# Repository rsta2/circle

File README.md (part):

Circle
======

Overview
--------

Circle is a C++ bare metal programming environment for the Raspberry Pi. It should be usable on most existing models (see "Support Status" below). Circle provides several ready-tested [C++ classes](doc/classes.txt) and [add-on libraries](addon/README), which can be used to control different hardware features of the Raspberry Pi. Together with Circle there are delivered several [sample programs](sample/README), which demonstrate the use of its classes. Circle can be used to create 32-bit or 64-bit bare metal applications.

Circle includes bigger (optional) third-party C-libraries for specific purposes in addon/ now. This is the reason why GitHub rates the project as a C-language-project. The main Circle libraries are written in C++ using classes instead. That's why it is called a C++ programming environment.

Disclaimer
----------

Circle is a free open-source project created by makers for makers. Because it targets bare-metal systems and is developed without formal QA or access to every hardware variant, it may not work as expected in all environments.

- **No warranty:** Circle is provided "as is" without any express or implied warranties, including merchantability, fitness for a particular purpose, or noninfringement.
- **Limited testing:** Contributors and maintainers test to the best of their ability but do not operate a dedicated testing department and cannot validate Circle on every device, bootloader version, or model revision.
- **User responsibility:** If you integrate Circle into a project - especially a commercial product (not recommended) - you are responsible for thoroughly testing the software in your target environment and for any consequences of its use.
- **Source-only distribution:** We publish Circle only as source code; no official binary releases are provided.
- **Risk acknowledgement:** By using Circle you acknowledge the residual risks associated with bare-metal development and accept responsibility for verifying suitability and safety for your use case.

Release 51.1.1
--------------

This hotfix release reverts a commit, which does not allow to use lld as the linker with Clang, which is planned to be used with circle-stdlib. Furthermore it comes with an additional sanity check for the 8BitDo gamepad drivers.

Release 51.1
------------

This release comes with **support for the Official 5" and 7" Touchscreens (v1 and v2)** with DSI interface **on the Raspberry Pi 5** in [addon/rp1dsi/](addon/rp1dsi). This can be tested with *sample/28-touchscreen* and *addon/lvgl/sample*. You have to set the `DSI_DISPLAY` variable in the respective *Makefile* to use the DSI displays.

Another attempt to **overcome the dropped USB MIDI events problem** on the Raspberry Pi 1-3 and Zero has been made. The *cmdline.txt* option `usbboost=` has been extended and gets a bit-masked decimal parameter now, where each bit 0-3 enables an option, which can help to fix such problems. See the [doc/cmdline.txt](doc/cmdline.txt) for a detailed description. `usbboost=15` enables all options, but does work only, when the USB MIDI controller is directly connected to the USB root port (without hub).

If you are using USB in FIQ mode on the Raspberry Pi 1-3 and Zero with the system option `USE_USB_FIQ`, you can try to enable the option `USB_MIDI_FIQ_COMPLETION` too to reduce the latency on delivering received MIDI events to the minimum. Your MIDI event packet handler must be able to run on `FIQ_LEVEL` in this case. Normally it runs on `IRQ_LEVEL`. Additionally you can define `USB_MIDI_CHECK_INCOMING` to validate incoming MIDI event packets, before calling the MIDI event packet handler.

More news:

* A new log severity `LogTrace` for frequent trace messages is introduced. Messages with this severity can be generated with the macro `LOGTRACE()`. Log messages of this kind are only displayed, when the option `loglevel=5` is specified in the file *cmdline.txt* on the SD card.
* A number of 8BitDo Xbox360 gamepads and keyboards is supported now.
* Support for USB mice with generic HID interface (3-0-0) has been added.
* FatFs has been updated to R0.16 with patch 2.

Fixes:

* An invalid handling of TCP ACK for fragmented modem sessions has been corrected. This also solved the issue of sending scrambled TCP data over low-speed/-quality network links.
* A race condition in `CSynchronizationEvent::Wait()` has been fixed, which could cause lost wake events, when this method had been called from an IRQ handler.
* A spurious hang caused by unexpected USB Disconnect events on cold boot has been fixed.
* Hidden WLAN SSIDs are supported now. You have to add the `scan_ssid=1` option for the hidden SSID to the file *wpa_supplicant.conf*.
* USB mass-storage gadget has speed auto-negotiation and a robust host reset/suspend handling now.
* Fixed that WLAN was unable to connect to eero7 router.

The 51st Step
-------------

This release offers a significantly improved implementation of the TCP/IP network stack. It supports TCP congestion control according to RFC 5681 with Fast Retransmit and Fast Recovery. Also the unnecessary copying of frames and data in the stack is largely prevented. This improves throughput very much, especially when a Raspberry Pi with 100 MBps Ethernet is connected to a Gigabit network.

The socket API is nearly unchanged, but the new `MSG_MORE` flag can be specified, when calling `CSocket::Send()` on TCP sockets, which prevents the immediate delivery of received data on the receiver side, when more data follows. `CSocket::Bind()` can be called with port 0 to bind to an ephemeral port, which can be requested using `CSocket::GetOwnPort()`. `CSocket::SendTo()` without preceding `Bind()` or `Connect()` is allowed too, which automatically assigns an ephemeral port.

Circle supports the extended C++ standard library support (LLVM libc++ port) in the [circle-stdlib](https://github.com/smuehlst/circle-stdlib) project in several ways (e.g. with the new `STDLIB_SUPPORT=4` level).

The recommended toolchain to build Circle applications is now based on GCC 15.2.Rel1. See the link in the Build section! Circle is built with `-std=c++17` by default now. There are options for selecting C++14 (previous default) and C++20 for the `configure` tool, beside the new `--kernel-max-size`, `--clang` and `--kasan` options. Enter `./configure --help` for more info!

The recommended firmware has been updated in *boot/*.

More new features:

* A `CDevice` instance can have property strings for vendor, product, serial number and function (e.g. the USB interface) now. These strings are assigned for all USB- and for NVMe devices, and can be used to distinguish devices of the same class. `CDeviceNameService::ListDevices()` can show these properties.
* The system option `USE_GPIO_MANAGER_FIQ` has been added. When an application needs multiple FIQ-triggered GPIO interrupt pins, the class `CGPIOPinFIQ` cannot be used. It is also not possible to use `CGPIOPinFIQ` together with the class `CGPIOManager` to handle more GPIO pins with IRQ. Now one can define this option to enable `CGPIOManager` and all GPIO pins, which use an interrupt, to use the FIQ to reduce GPIO interrupt latency. The GPIO interrupt handler will run at `FIQ_LEVEL` then.
* `CGPIOClock::StartRate()` can use fractional dividers on Raspberry 1-4. Before only integer dividers were supported. Now automatically a fractional divider will be used with MASH 1, if necessary.
* The class `CPipe` (an unidirectional inter-process communication channel using
a FIFO) and the methods `CMutex::TryAcquire()` and `CSemaphore::DownWithTimeout()` have been added to the scheduler library. `CSemaphore` objects can have the initial count of zero now. *test/pipe* demonstrates `CPipe`.
* Sound devices allow writing and reading samples in the `SoundFormatFloat32` now. Samples must be of the data type `float` in the range \[-1.0 .. 1.0\] in this case. *sample/34-sounddevices* and *test/sound-controller* can be configured to use this.
* The class `CPWMSoundBaseDevice` supports the M/S PWM mode, which is also the default now. This should lead to a better audio quality and suppresses hum, when the PWM signal is delivered via the GPIO header.
* The class `CEMMCDevice` in [addon/SDCard](addon/SDCard) supports external SDIO breakout boards at GPIO22-27 now as device "emmc2" and "SD2:" in FatFs. This does work with the EMMC host only (not with `USE_SDHOST`). On the Raspberry Pi 4 and CM4 the class can be instantiated twice with different device selector parameter specified to the constructor.
* A `CSSD1309Display` graphics-mode driver for the SSD1309 128x64 OLED display controller (I2C and SPI) has been added to [addon/display](addon/display).
* A `CMCP23017` driver for the MCP23017 16-bit I2C GPIO expander has been added to the [addon/gpio](addon/gpio).
* The MPU-6050 driver in [addon/sensor](addon/sensor) has been extended and returns a scaled acceleration and gyroscope output now. The acceleration and gyroscope range and digital low-pass filter bandwidth can be configured. The sample adds a graphics mode.
* The serial bootloader images are much smaller now and are able to load kernel images of up to about 8 MB.

A number of fixes have been applied:

* `CGPIOClock::Stop()` was operating on the wrong clock. This caused a stop of the UART clock, when GPIOClock2 was started.
* `CMachineInfo::GetClockRate()` now favors the firmware function `GET_CLOCK_RATE_MEASURED` over `GET_CLOCK_RATE`, which reported a wrong Core clock rate, when `CCPUThrottle` was used. The reported value is rounded to the closest MHz value.
* The *cmdline.txt* option `wm8960tune=` has been added as a workaround. Add the given value to the fractional (K) part of PLL1 input/output frequency ratio (treated as 24-digit binary number) of the WM8960 Codec to suppress clicks/pops (range -10000 to 10000, default 0).
* There have been multiple issues with the handling of TCP FIN packets, which were leading to a delayed termination of connections.
* There was a problem found in the scheduler using KASan, which was accessing a task object after deleting it.

Features
--------

> Only the features with a "x" or other info are currently supported on the Raspberry Pi 5.

Circle supports the following features:

| Group                 | Features                                            | Raspberry Pi 5 |
|-----------------------|-----------------------------------------------------|----------------|
| C++ build environment | AArch32 and AArch64 support                         | AArch64 only   |
|                       | Basic library functions (e.g. new and delete)       | x              |
|                       | Enables all CPU caches using the MMU                | x              |
|                       | Interrupt support (IRQ and FIQ)                     | IRQ only       |
|                       | Multi-core support (Raspberry Pi 2, 3 and 4)        | x              |
|                       | Cooperative non-preemptive scheduler                | x              |
|                       | CPU clock rate management                           | x              |
|                       | Clang/LLVM support (experimental)                   | x              |
|                       |                                                     |                |
| Debug support         | Kernel logging to screen, UART and/or syslog server | x              |
|                       | C-assertions with stack trace                       | x              |
|                       | Hardware exception handler with stack trace         | x              |
|                       | GDB support using rpi_stub (Raspberry Pi 2 and 3)   |                |
|                       | Serial bootloader (by David Welch) included         | x              |
|                       | Software profiling support (single-core)            | x              |
|                       | QEMU support                                        |                |
|                       | Kernel Address Sanitizer support                    | x              |
|                       |                                                     |                |
| SoC devices           | GPIO pins (with interrupt, Act LED) and clocks      | x              |
|                       | Frame buffer (screen driver with escape sequences)  | limited        |
|                       | UART(s) (Polling and interrupt driver)              | x              |
|                       | System timer (with kernel timers)                   | x              |
|                       | Platform DMA controller                             | DMA40 only     |
|                       | RP1 platform DMA controller (Raspberry Pi 5 only)   | x              |
|                       | EMMC SD card interface driver                       | x              |
|                       | SDHOST SD card interface driver (Raspberry Pi 1-3)  |                |
|                       | PWM output (2 channels)                             | 4 channels     |
|                       | PWM sound output (on headphone jack)                | with adapter   |
|                       | I2C master(s) and slave                             | masters only   |
|                       | SPI0 master (Polling and DMA driver)                | x              |
|                       | SPI1 auxiliary master (Polling)                     |                |
|                       | SPI3-6 masters of Raspberry Pi 4 (Polling)          | SPI1-3 and 5   |
|                       | SMI master                                          |                |
|                       | I2S sound output and input                          | x              |
|                       | HDMI sound output (without VCHIQ)                   | x              |
|                       | Hardware random number generator                    | x              |
|                       | Watchdog device                                     | x              |
|                       | Official 7" Raspberry Pi touch screen (v1 only)     | 5" and 7" v1/2 |
|                       | VCHIQ interface and audio service drivers           |                |
|                       | BCM54213PE Gigabit Ethernet NIC of Raspberry Pi 4   |                |
|                       | MACB / GEM Gigabit Ethernet NIC of Raspberry Pi 5   | x              |
|                       | Wireless LAN access                                 | x              |
|                       | Driver for XPT2046-based touch screens              | x              |
|                       | NVMe SSD driver for Raspberry Pi 5 (experimental)   | x              |
|                       |                                                     |                |
| USB                   | Host controller interface (HCI) drivers             | x              |
|                       | Standard hub driver (USB 2.0 only)                  | x              |
|                       | HID class device drivers (keyboard, mouse, gamepad) | x              |
|                       | Driver for on-board Ethernet device (SMSC951x)      |                |
|                       | Driver for on-board Ethernet device (LAN7800)       |                |
|                       | Driver for CDC Ethernet devices (RTL815x, QEMU)     |                |
|                       | Driver for USB mass storage devices (bulk only)     | x              |
|                       | Driver for USB floppy disk devices (experimental)   | x              |
|                       | Driver for USB audio streaming devices (RPi 4 only) | x              |
|                       | Drivers for different USB serial devices            | x              |
|                       | Audio class MIDI input support                      | x              |
|                       | Touchscreen driver (digitizer mode)                 | x              |
|                       | Printer driver                                      | x              |
|                       | MIDI gadget driver                                  |                |
|                       | Serial CDC gadget driver                            |                |
|                       | Mass-storage device gadget driver                   |                |
|                       |                                                     |                |
| File systems          | Internal FAT driver (limited function)              | x              |
|                       | FatFs driver (full function, by ChaN)               | x              |
|                       |                                                     |                |
| TCP/IP networking     | Protocols: ARP, IP, ICMP, IGMP, UDP, TCP            | x              |
|                       | Clients: DHCP, DNS, NTP, HTTP, Syslog, MQTT, mDNS   | x              |
|                       | Servers: HTTP, TFTP                                 | x              |
|                       | BSD-like C++ socket API                             | x              |
|                       |                                                     |                |
| Graphics              | OpenGL ES 1.1 and 2.0, OpenVG 1.1, EGL 1.4          |                |
|                       | (not on Raspberry Pi 4)                             |                |
|                       | uGUI (by Achim Doebler)                             |                |
|                       | LVGL (by LVGL Kft)                                  | x              |
|                       | 2D graphics class in base library                   | x              |
|                       |                                                     |                |
| Not supported         | Bluetooth                                           |                |

Support Status
--------------

This table lists the support status for the different Raspberry Pi models. Not listed models are not supported.

| Model                   | Status           | Remarks                          |
|-------------------------|------------------|----------------------------------|
| Raspberry Pi Model A    | Should work      |                                  |
| Raspberry Pi Model B R1 | Should work      |                                  |
| Raspberry Pi Model B R2 | Tested           |                                  |
| Raspberry Pi Model A+   | Tested           |                                  |
| Raspberry Pi Model B+   | Tested           |                                  |
|                         |                  |                                  |
| Raspberry Pi Zero       | Tested           |                                  |
| Raspberry Pi Zero W     | Tested           |                                  |
| Raspberry Pi Zero 2 W   | Tested           | WLAN unknown for new revision    |
|                         |                  |                                  |
| Raspberry Pi 2 Model B  | Tested           |                                  |
| Raspberry Pi 3 Model B  | Tested           |                                  |
| Raspberry Pi 3 Model A+ | Tested           |                                  |
| Raspberry Pi 3 Model B+ | Tested           |                                  |
| Raspberry Pi 4 Model B  | Tested           |                                  |
| Raspberry Pi 400        | Tested           |                                  |
| Raspberry Pi 5          | Tested           | With BCM2712 C1 and D0 steppings |
| Raspberry Pi 500        | Unknown          |                                  |
|                         |                  |                                  |
| Compute Module          | Reported to work | Unknown which devices work       |
| Compute Module 3        | Should work      |                                  |
| Compute Module 3+       | Reported to work | WLAN unknown                     |
| Compute Module 4        | Tested           | WLAN unknown                     |
| Compute Module 4S       | Unknown          |                                  |
| Compute Module 5        | Reported to work | Unknown which devices work       |
| Compute Module Zero     | Reported to work |                                  |

Build
-----

> For building 64-bit applications (AArch64) see the next section.

> Circle does not support 32-bit applications on the Raspberry Pi 5.

This describes building on PC Linux. See the file [doc/windows-build.txt](doc/windows-build.txt) for information about building on Windows. If building for the Raspberry Pi 1 you need a [toolchain](http://elinux.org/Rpi_Software#ARM) for the ARM1176JZF core (with EABI support). For Raspberry Pi 2/3/4 you need a toolchain with Cortex-A7/-A53/-A72 support. A toolchain, which works for all of these, can be downloaded [here](https://gitlab.arm.com/tooling/gnu-toolchains-for-arm). Circle has been tested with the version *15.2.Rel1* (arm-gnu-toolchain-15.2.rel1-x86_64-arm-none-eabi.tar.xz) from this website. This is the recommended toolchain for AArch32 builds.

First edit the file *Rules.mk* and set the Raspberry Pi version (*RASPPI*, 1, 2, 3 or 4) and the *PREFIX* of your toolchain commands. Alternatively you can create a *Config.mk* file (which is ignored by git) and set the Raspberry Pi version and the *PREFIX* variable to the prefix of your compiler like this (don't forget the dash at the end):

```
RASPPI = 1
PREFIX = arm-none-eabi-
```

The following table gives support for selecting the right *RASPPI* value:

| RASPPI | Target         | Models                   | Optimized for |
| ------ | -------------- | ------------------------ | ------------- |
|      1 | kernel.img     | A, B, A+, B+, Zero, (CM) | ARM1176JZF-S  |
|      2 | kernel7.img    | 2, 3, Zero 2, (CM3)      | Cortex-A7     |
|      3 | kernel8-32.img | 3, Zero 2, (CM3)         | Cortex-A53    |
|      4 | kernel7l.img   | 4B, 400, CM4             | Cortex-A72    |

For a binary distribution you should do one build with *RASPPI = 1*, one with *RASPPI = 2* and one build with *RASPPI = 4* and include the created files *kernel.img*, *kernel7.img* and *kernel7l.img*. Optionally you can do a build with *RASPPI = 3* and add the created file *kernel8-32.img* to provide an optimized version for the Raspberry Pi 3.

The configuration file *Config.mk* can be created using the `configure` tool too. Please enter `./configure -h` for help on using it!

> There are a number of configurable system options in the file [include/circle/sysconfig.h](include/circle/sysconfig.h). Please have a look into this file to learn, how you can configure Circle for your purposes. Some hardware configurations may require modifications to these options (e.g. using USB on the CM4).

Then go to the build root of Circle and do:

```
./makeall clean
./makeall
```

By default only the Circle libraries are built. To build a sample program after `makeall` go to its subdirectory and do `make`.

You can also build Circle on the Raspberry Pi itself (set `PREFIX =` (empty)) on Raspbian but you need some method to put the *kernel.img* file onto the SD(HC) card. With an external USB card reader on model B+ or Raspberry Pi 2/3/4 model B (4 USB ports) this should be no problem.

AArch64
-------

Circle supports building 64-bit applications, which can be run on the Raspberry Pi 3, 4 or 5. There are also Raspberry Pi 2 versions and the Raspberry Pi Zero 2, which are based on the BCM2837 SoC. These Raspberry Pi versions can be used too (with `RASPPI = 3`).

The recommended toolchain to build 64-bit applications with Circle can be downloaded [here](https://gitlab.arm.com/tooling/gnu-toolchains-for-arm). Circle has been tested with the version *15.2.Rel1* (arm-gnu-toolchain-15.2.rel1-x86_64-aarch64-none-elf.tar.xz) from this website. This is the recommended toolchain for AArch64 builds.

There are distro-provided toolchains on certain Linux platforms (e.g. *g++-aarch64-linux-gnu* on Ubuntu or *gcc-c++-aarch64-linux-gnu* on Fedora), which may work with Circle and can be a quick way to use it, but you have to test this by yourself. If you encounter problems (e.g. no reaction at all, link failure with external library) using a distro-provided toolchain, please try the recommended toolchain (see above) first, before reporting an issue.

First edit the file *Rules.mk* and set the Raspberry Pi architecture (*AARCH*, 32 or 64) and the *PREFIX64* of your toolchain commands. The *RASPPI* variable has to be set to 3, 4 or 5 for `AARCH = 64`. Alternatively you can create a *Config.mk* file (which is ignored by git) and set the Raspberry Pi architecture and the *PREFIX64* variable to the prefix of your compiler like this (don't forget the dash at the end):

```
AARCH = 64
RASPPI = 3
PREFIX64 = aarch64-none-elf-
```

The configuration file *Config.mk* can be created using the `configure` tool too. Please enter `./configure -h` for help on using it!

Then go to the build root of Circle and do:

```
./makeall clean
./makeall
```

By default only the Circle libraries are built. To build a sample program after `makeall` go to its subdirectory and do `make`.

Installation
------------

Copy the Raspberry Pi firmware (from boot/ directory, do *make* there to get them) files along with the *kernel\*.img* (from sample/ subdirectory) to a SD(HC) card with FAT file system.

It is now always recommended to copy the file *config32.txt* (for 32-bit mode) or *config64.txt* (for 64-bit mode) from the boot/ directory to the SD(HC) card and to rename it to *config.txt* there. These files are especially required to enable FIQ use on the Raspberry Pi 4. Furthermore the additional file *armstub7-rpi4.bin* (for 32-bit mode) or *armstub8-rpi4.bin* (for 64-bit mode) is required on the SD card then. Please see [boot/README](boot/README) for information on how to build these files.

Finally put the SD(HC) card into the Raspberry Pi.

Directories
-----------

* include: The common header files, most class headers are in the include/circle/ subdirectory.
* lib: The Circle class implementation and support files (other libraries are in subdirectories of lib/).
* sample: Several sample applications using Circle in different subdirectories. The main function is implemented in the CKernel class.
* addon: Contains contributed libraries and samples (has to be build manually).
* app: Place your own applications here. If you have own libraries put them into app/lib/.
* boot: Do *make* in this directory to get the Raspberry Pi firmware files required to boot.
* doc: Additional documentation files.
* test: Several test programs, which test different features of Circle on the Raspberry Pi hardware.
* tools: Tools for building Circle and for using Circle more comfortable (e.g. a serial bootloader).
* unittest: Several unit test programs, which run on the development machine.

Classes
-------

The following C++ classes were added to Circle:

Scheduler library

* CPipe: Unidirectional interprocess communication channel using a FIFO
* CPipeFile: Read or Write endpoint of a CPipe channel
 
Net library

* CNetBuffer: Generic frame/packet buffer for network protocol handling
* CNetBufferQueue: FIFO queue for CNetBuffer objects
* CReassemblyQueue: Reassembly queue for the TCP receiver

The available Circle classes are listed in the file [doc/classes.txt](doc/classes.txt). If you have Doxygen installed on your computer you can build a [class documentation](doc/html/index.html) in doc/html/ using:

`./makedoc`

At the moment there are only a few classes described in detail for Doxygen.

Additional Topics
-----------------

* [Standard library support](doc/stdlib-support.txt)
* [Dynamic memory management and the "new" operator](doc/new-operator.txt)
* [DMA buffer requirements](doc/dma-buffer-requirements.txt)
* [Serial bootloader support](doc/bootloader.txt)
* [Multi-core support](doc/multicore.txt)
* [USB plug-and-play](doc/usb-plug-and-play.txt)
* [Debugging support](doc/debug.txt)
* [JTAG debugging](doc/debug-jtag.txt)
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
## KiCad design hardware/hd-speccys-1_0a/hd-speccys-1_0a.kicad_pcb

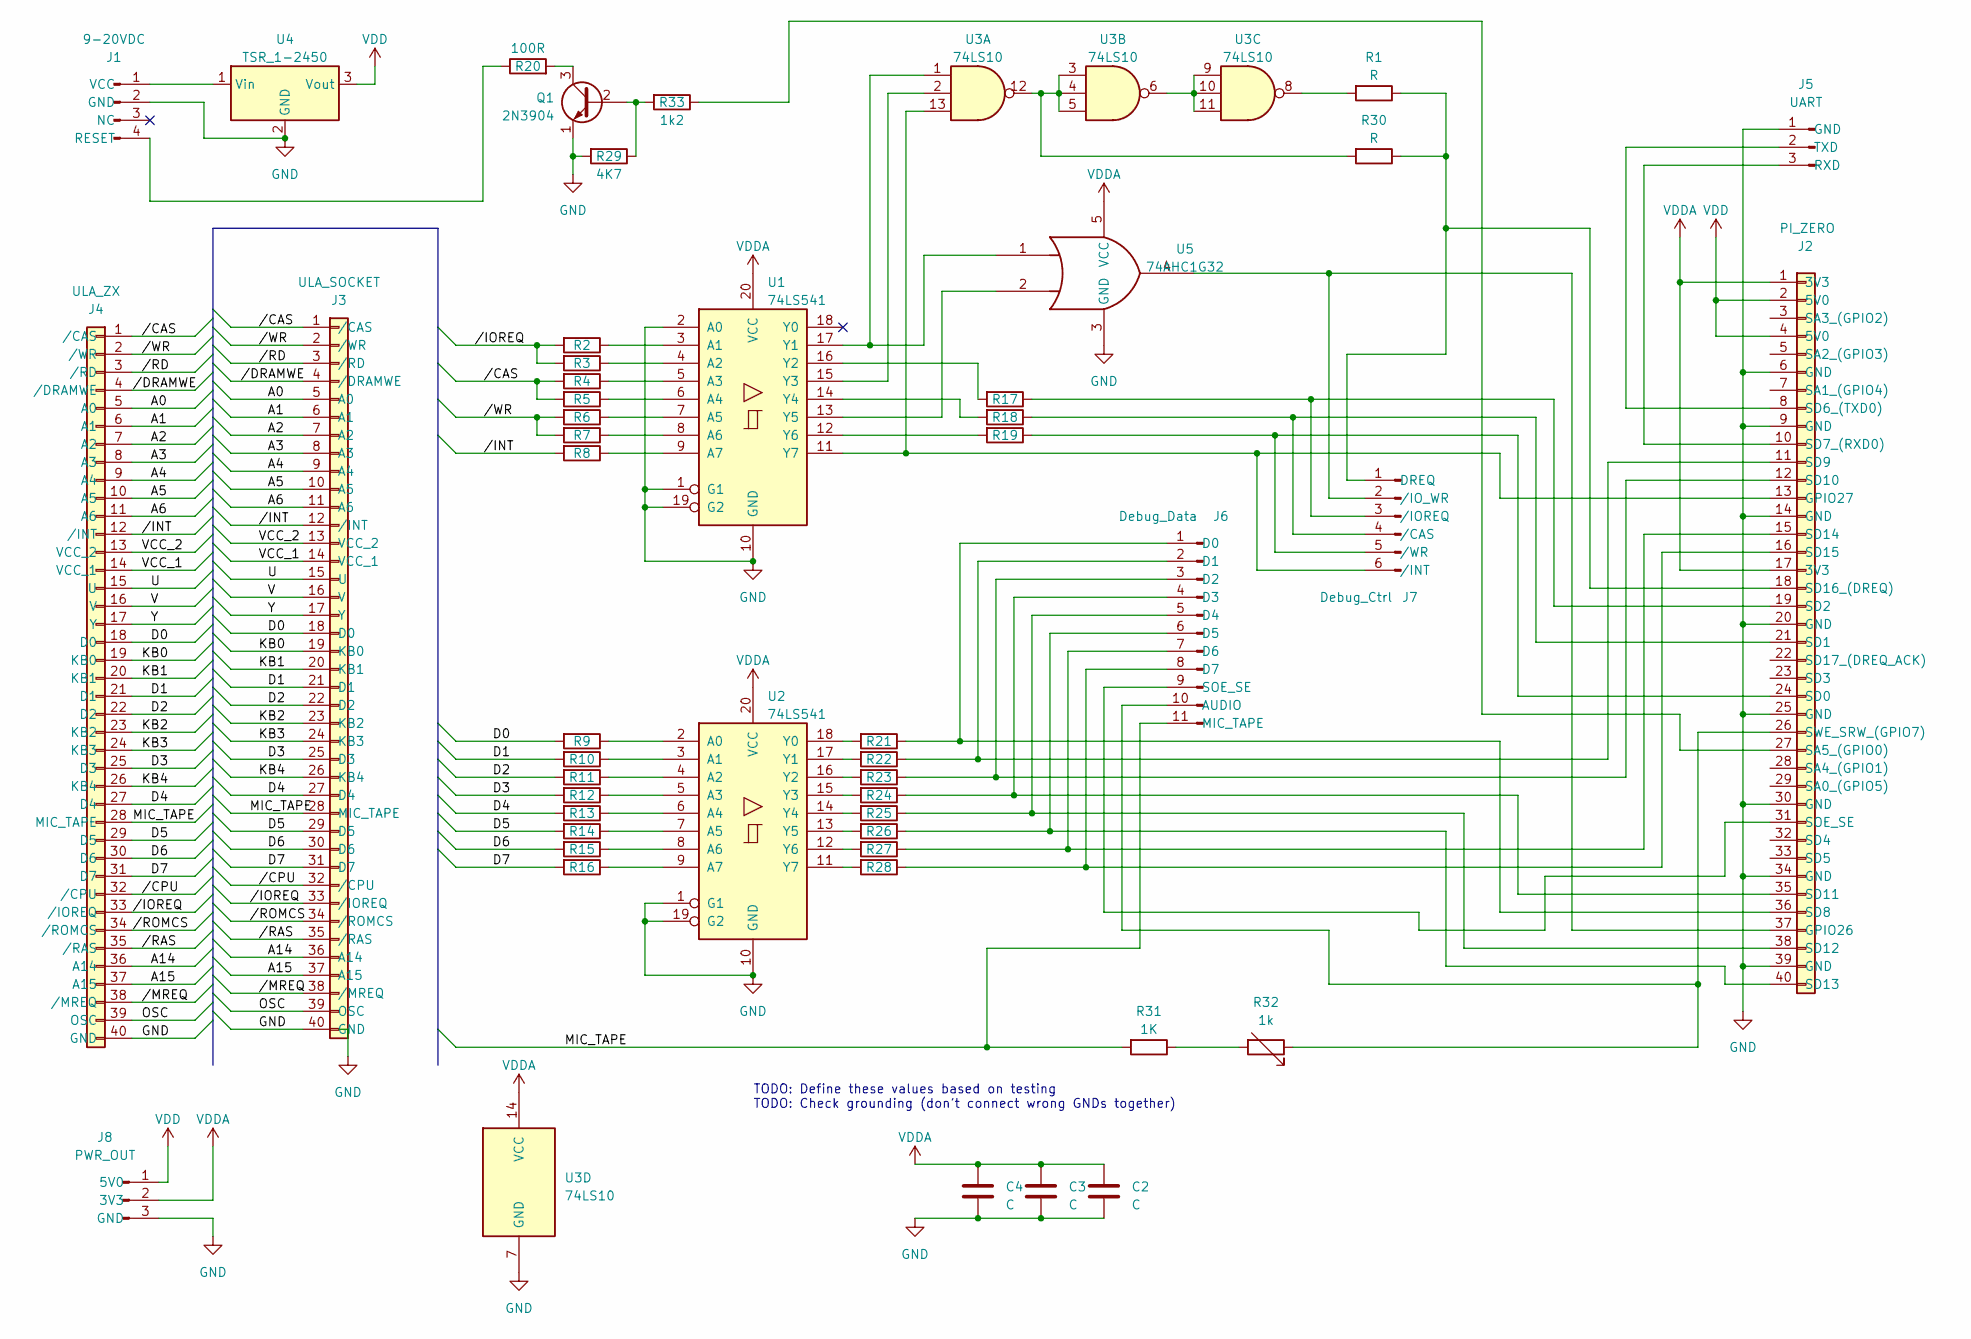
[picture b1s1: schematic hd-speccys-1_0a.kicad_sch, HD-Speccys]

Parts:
C2, C3, C4: C; C_0603_1608Metric_Pad1.08x0.95mm_HandSolder
J1: 9-20VDC; PinHeader_1x04_P2.54mm_Horizontal
J2: PI_ZERO; Raspberry_Pi_Zero_Socketed_THT_FaceDown_MountingHoles
J3: ULA_SOCKET; DIP-40_W15.24mm_Socket
J4: ULA_ZX; DIP-40_W15.24mm_Socket
J5: UART; PinHeader_1x03_P2.54mm_Vertical
J6: Debug_Data; PinHeader_1x11_P2.54mm_Vertical
J7: Debug_Ctrl; PinHeader_1x06_P2.54mm_Vertical
J8: PWR_OUT; PinHeader_1x03_P2.54mm_Vertical
Q1: 2N3904; TO-92_Inline
R1, R2, R3, R4, R5, R6, R7, R8, R9, R10, R11, R12, R13, R14, R15, R16, R17, R18, R19, R21, R22, R23, R24, R25, R26, R27, R28, R30: R; R_0603_1608Metric_Pad0.98x0.95mm_HandSolder
R20: 100R; R_0603_1608Metric_Pad0.98x0.95mm_HandSolder
R29: 4K7; R_0603_1608Metric_Pad0.98x0.95mm_HandSolder
R31: 1K; R_0603_1608Metric_Pad0.98x0.95mm_HandSolder
R32: 1k; Potentiometer_Bourns_TC33X_Vertical
R33: 1k2; R_0603_1608Metric_Pad0.98x0.95mm_HandSolder
U1, U2: 74LS541; TSSOP-20_4.4x6.5mm_P0.65mm
U3: 74LS10; TSSOP-14_4.4x5mm_P0.65mm
U4: TSR_1-2450; Converter_DCDC_Murata_OKI-78SR_Horizontal
U5: 74AHC1G32; SOT-353_SC-70-5_Handsoldering

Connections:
GND: C2.2, C3.2, C4.2, J1.2 (GND), J2.6 (GND), J2.9 (GND), J2.14 (GND), J2.20 (GND), J2.25 (GND), J2.30 (GND), J2.34 (GND), J2.39 (GND), J3.40 (GND), J4.40 (GND), J5.1 (GND), J8.3 (GND), Q1.1 (E), R29.2, U1.1 (G1), U1.2 (A0), U1.10 (GND), U1.19 (G2), U2.1 (G1), U2.10 (GND), U2.19 (G2), U3.7 (GND), U4.2 (GND), U5.3 (GND)
unnamed: J1.4 (RESET), R20.1
unnamed: J1.1 (VCC), U4.1 (Vin)
unnamed: J2.37 (GPIO26), J7.2 (/IO_WR), U5.4
unnamed: J2.13 (GPIO27), J7.6 (/INT), U1.11 (Y7), U3.13
unnamed: J2.27 (SA5_(GPIO0)), R33.1
unnamed: J2.24 (SD0), J7.5 (/WR), R19.1
unnamed: J2.21 (SD1), J7.4 (/CAS), R18.1
unnamed: J2.19 (SD2), J7.3 (/IOREQ), R17.1
unnamed: J2.8 (SD6_(TXD0)), J5.2 (TXD)
unnamed: J2.10 (SD7_(RXD0)), J5.3 (RXD)
unnamed: J2.36 (SD8), J6.1 (D0), R21.1
unnamed: J2.11 (SD9), J6.2 (D1), R22.1
unnamed: J2.12 (SD10), J6.3 (D2), R23.1
unnamed: J2.35 (SD11), J6.4 (D3), R24.1
unnamed: J2.38 (SD12), J6.5 (D4), R25.1
unnamed: J2.40 (SD13), J6.6 (D5), R26.1
unnamed: J2.15 (SD14), J6.7 (D6), R27.1
unnamed: J2.16 (SD15), J6.8 (D7), R28.1
unnamed: J2.18 (SD16_(DREQ)), J7.1 (DREQ), R1.1, R30.1
unnamed: J2.31 (SOE_SE), J6.9 (SOE_SE)
unnamed: J2.26 (SWE_SRW_(GPIO7)), J6.10 (AUDIO), R32.1
unnamed: J3.5 (A0), J4.5 (A0)
unnamed: J3.6 (A1), J4.6 (A1)
unnamed: J3.7 (A2), J4.7 (A2)
unnamed: J3.8 (A3), J4.8 (A3)
unnamed: J3.9 (A4), J4.9 (A4)
unnamed: J3.10 (A5), J4.10 (A5)
unnamed: J3.11 (A6), J4.11 (A6)
unnamed: J3.36 (A14), J4.36 (A14)
unnamed: J3.37 (A15), J4.37 (A15)
unnamed: J3.18 (D0), J4.18 (D0), R9.2
unnamed: J3.21 (D1), J4.21 (D1), R10.2
unnamed: J3.22 (D2), J4.22 (D2), R11.2
unnamed: J3.25 (D3), J4.25 (D3), R12.2
unnamed: J3.27 (D4), J4.27 (D4), R13.2
unnamed: J3.29 (D5), J4.29 (D5), R14.2
unnamed: J3.30 (D6), J4.30 (D6), R15.2
unnamed: J3.31 (D7), J4.31 (D7), R16.2
unnamed: J3.19 (KB0), J4.19 (KB0)
unnamed: J3.20 (KB1), J4.20 (KB1)
unnamed: J3.23 (KB2), J4.23 (KB2)
unnamed: J3.24 (KB3), J4.24 (KB3)
unnamed: J3.26 (KB4), J4.26 (KB4)
unnamed: J3.28 (MIC_TAPE), J4.28 (MIC_TAPE), J6.11 (MIC_TAPE), R31.2
unnamed: J3.39 (OSC), J4.39 (OSC)
unnamed: J3.15 (U), J4.15 (U)
unnamed: J3.16 (V), J4.16 (V)
unnamed: J3.14 (VCC_1), J4.14 (VCC_1)
unnamed: J3.13 (VCC_2), J4.13 (VCC_2)
unnamed: J3.17 (Y), J4.17 (Y)
unnamed: J3.1 (/CAS), J4.1 (/CAS), R4.2, R5.2
unnamed: J3.32 (/CPU), J4.32 (/CPU)
unnamed: J3.4 (/DRAMWE), J4.4 (/DRAMWE)
unnamed: J3.12 (/INT), J4.12 (/INT), R8.2
unnamed: J3.33 (/IOREQ), J4.33 (/IOREQ), R2.2, R3.2
unnamed: J3.38 (/MREQ), J4.38 (/MREQ)
unnamed: J3.35 (/RAS), J4.35 (/RAS)
unnamed: J3.3 (/RD), J4.3 (/RD)
unnamed: J3.34 (/ROMCS), J4.34 (/ROMCS)
unnamed: J3.2 (/WR), J4.2 (/WR), R6.2, R7.2
unnamed: Q1.2 (B), R29.1, R33.2
unnamed: Q1.3 (C), R20.2
unnamed: R1.2, U3.8
unnamed: R30.2, U3.3, U3.4, U3.5, U3.12
unnamed: R31.1, R32.2
unnamed: R2.1, U1.3 (A1)
unnamed: R3.1, U1.4 (A2)
unnamed: R4.1, U1.5 (A3)
unnamed: R5.1, U1.6 (A4)
unnamed: R6.1, U1.7 (A5)
unnamed: R7.1, U1.8 (A6)
unnamed: R8.1, U1.9 (A7)
unnamed: U1.17 (Y1), U3.1, U5.1
unnamed: R17.2, U1.16 (Y2)
unnamed: U1.15 (Y3), U3.2
unnamed: R18.2, U1.14 (Y4)
unnamed: U1.13 (Y5), U5.2
unnamed: R19.2, U1.12 (Y6)
unnamed: R9.1, U2.2 (A0)
unnamed: R10.1, U2.3 (A1)
unnamed: R11.1, U2.4 (A2)
unnamed: R12.1, U2.5 (A3)
unnamed: R13.1, U2.6 (A4)
unnamed: R14.1, U2.7 (A5)
unnamed: R15.1, U2.8 (A6)
unnamed: R16.1, U2.9 (A7)
unnamed: R21.2, U2.18 (Y0)
unnamed: R22.2, U2.17 (Y1)
unnamed: R23.2, U2.16 (Y2)
unnamed: R24.2, U2.15 (Y3)
unnamed: R25.2, U2.14 (Y4)
unnamed: R26.2, U2.13 (Y5)
unnamed: R27.2, U2.12 (Y6)
unnamed: R28.2, U2.11 (Y7)
unnamed: U3.6, U3.9, U3.10, U3.11
VDD: J2.2 (5V0), J2.4 (5V0), J8.1 (5V0), U4.3 (Vout)
VDDA: C2.1, C3.1, C4.1, J2.1 (3V3), J2.17 (3V3), J8.2 (3V3), U1.20 (VCC), U2.20 (VCC), U3.14 (VCC), U5.5 (VCC)

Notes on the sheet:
TODO: Define these values based on testing TODO: Check grounding (don't connect wrong GNDs together)

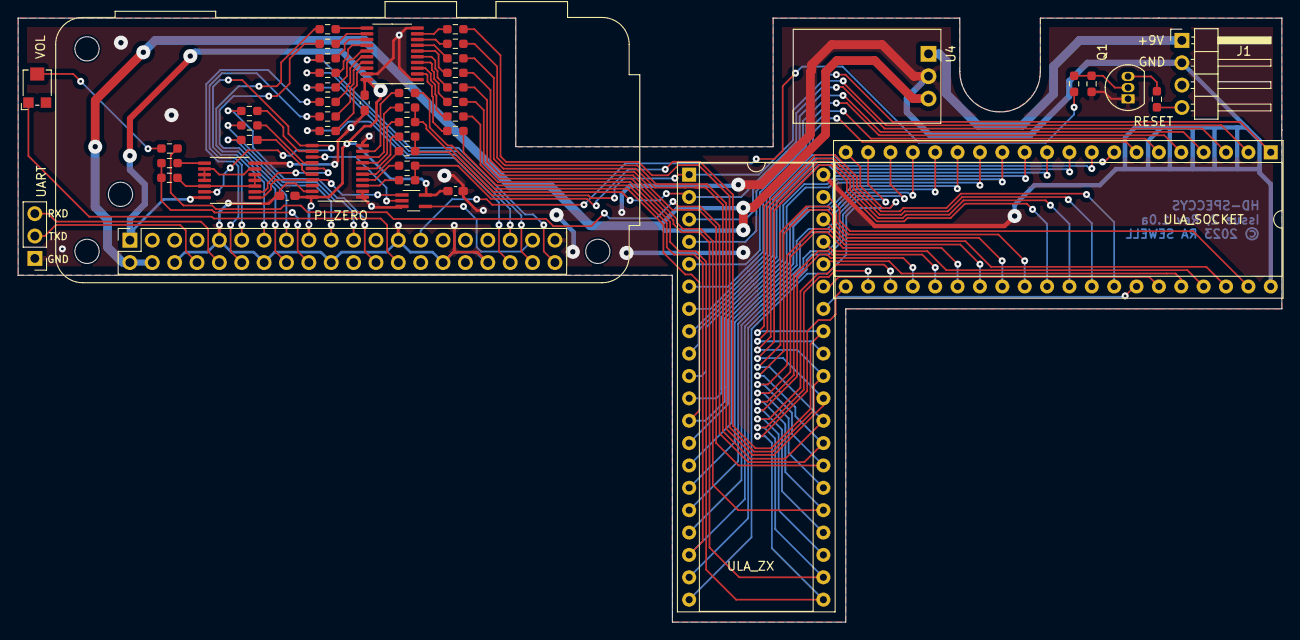
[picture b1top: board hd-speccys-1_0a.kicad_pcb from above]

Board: 2 copper layers, 143.5 x 68.6 mm, 47 parts (0 on the bottom side), 97 nets.

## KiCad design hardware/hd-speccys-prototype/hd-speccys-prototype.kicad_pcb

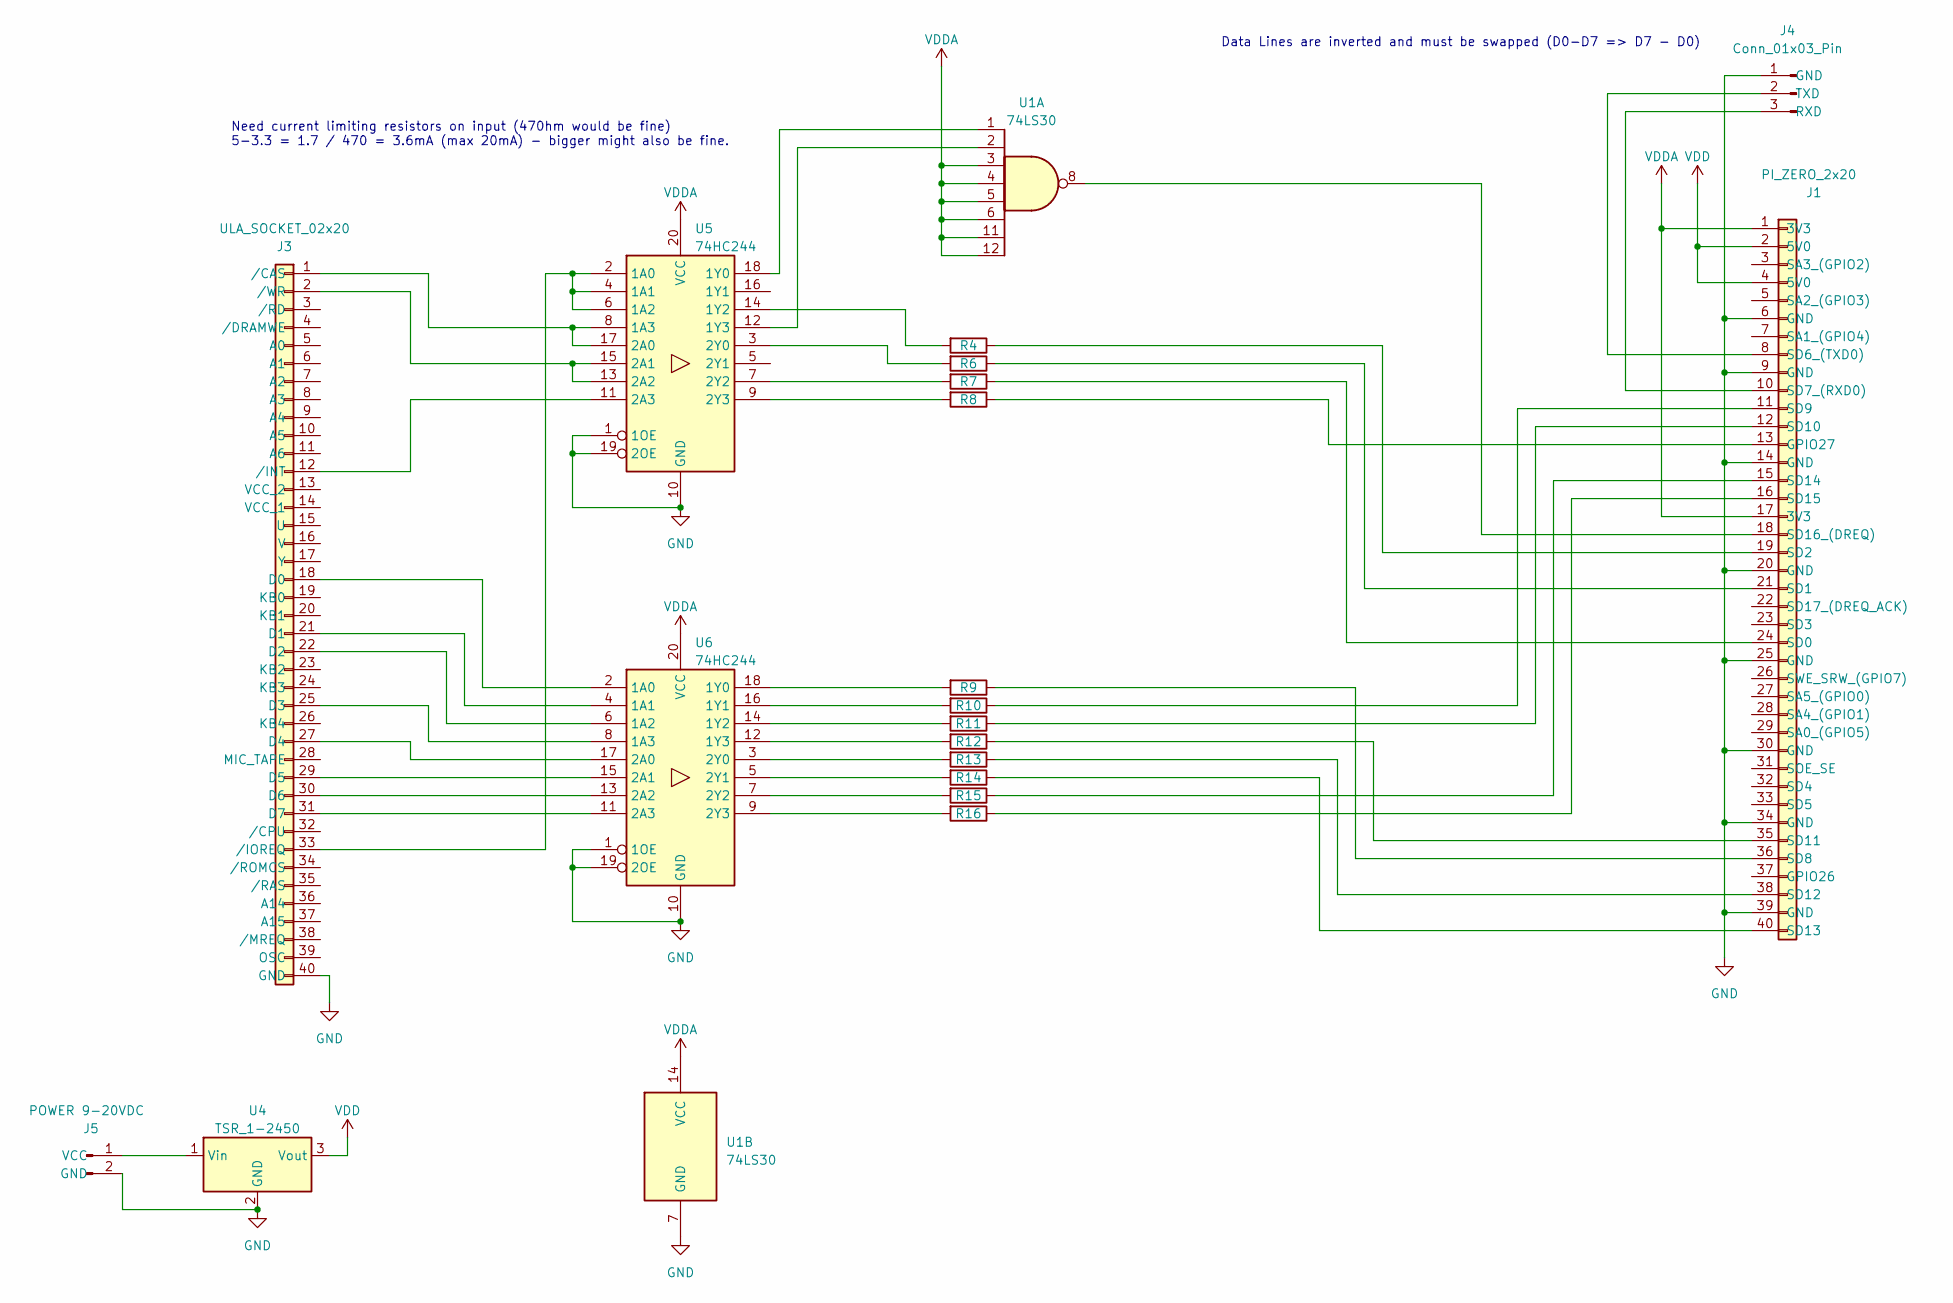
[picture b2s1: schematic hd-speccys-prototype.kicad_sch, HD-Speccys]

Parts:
J1: PI_ZERO_2x20; Raspberry_Pi_Zero_Socketed_THT_FaceDown_MountingHoles
J3: ULA_SOCKET_02x20; DIP-40_W15.24mm_Socket
J4: Conn_01x03_Pin; PinHeader_1x03_P2.54mm_Vertical
J5: POWER 9-20VDC; PinHeader_1x02_P2.54mm_Horizontal
R4, R6, R7, R8, R9, R10, R11, R12, R13, R14, R15, R16: R; R_0603_1608Metric_Pad0.98x0.95mm_HandSolder
U1: 74LS30; DIP-14_W7.62mm
U4: TSR_1-2450; Converter_DCDC_TRACO_TSR-1_THT
U5, U6: 74HC244; DIP-20_W7.62mm_Socket

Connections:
GND: J1.6 (GND), J1.9 (GND), J1.14 (GND), J1.20 (GND), J1.25 (GND), J1.30 (GND), J1.34 (GND), J1.39 (GND), J3.40 (GND), J4.1 (GND), J5.2 (GND), U1.7 (GND), U4.2 (GND), U5.1 (1OE), U5.10 (GND), U5.19 (2OE), U6.1 (1OE), U6.10 (GND), U6.19 (2OE)
unnamed: J1.13 (GPIO27), R8.1
unnamed: J1.24 (SD0), R7.1
unnamed: J1.21 (SD1), R6.1
unnamed: J1.19 (SD2), R4.1
unnamed: J1.8 (SD6_(TXD0)), J4.2 (TXD)
unnamed: J1.10 (SD7_(RXD0)), J4.3 (RXD)
unnamed: J1.36 (SD8), R9.1
unnamed: J1.11 (SD9), R10.1
unnamed: J1.12 (SD10), R11.1
unnamed: J1.35 (SD11), R12.1
unnamed: J1.38 (SD12), R13.1
unnamed: J1.40 (SD13), R14.1
unnamed: J1.15 (SD14), R15.1
unnamed: J1.16 (SD15), R16.1
unnamed: J1.18 (SD16_(DREQ)), U1.8
unnamed: J3.18 (D0), U6.2 (1A0)
unnamed: J3.21 (D1), U6.4 (1A1)
unnamed: J3.22 (D2), U6.6 (1A2)
unnamed: J3.25 (D3), U6.8 (1A3)
unnamed: J3.27 (D4), U6.17 (2A0)
unnamed: J3.29 (D5), U6.15 (2A1)
unnamed: J3.30 (D6), U6.13 (2A2)
unnamed: J3.31 (D7), U6.11 (2A3)
unnamed: J3.1 (/CAS), U5.8 (1A3), U5.17 (2A0)
unnamed: J3.12 (/INT), U5.11 (2A3)
unnamed: J3.33 (/IOREQ), U5.2 (1A0), U5.4 (1A1), U5.6 (1A2)
unnamed: J3.2 (/WR), U5.13 (2A2), U5.15 (2A1)
unnamed: J5.1 (VCC), U4.1 (Vin)
unnamed: U1.1, U5.18 (1Y0)
unnamed: R4.2, U5.14 (1Y2)
unnamed: U1.2, U5.12 (1Y3)
unnamed: R6.2, U5.3 (2Y0)
unnamed: R7.2, U5.7 (2Y2)
unnamed: R8.2, U5.9 (2Y3)
unnamed: R9.2, U6.18 (1Y0)
unnamed: R10.2, U6.16 (1Y1)
unnamed: R11.2, U6.14 (1Y2)
unnamed: R12.2, U6.12 (1Y3)
unnamed: R13.2, U6.3 (2Y0)
unnamed: R14.2, U6.5 (2Y1)
unnamed: R15.2, U6.7 (2Y2)
unnamed: R16.2, U6.9 (2Y3)
VDD: J1.2 (5V0), J1.4 (5V0), U4.3 (Vout)
VDDA: J1.1 (3V3), J1.17 (3V3), U1.3, U1.4, U1.5, U1.6, U1.11, U1.12, U1.14 (VCC), U5.20 (VCC), U6.20 (VCC)

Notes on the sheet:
Data Lines are inverted and must be swapped (D0-D7 => D7 - D0)
Need current limiting resistors on input (470hm would be fine) 5-3.3 = 1.7 / 470 = 3.6mA (max 20mA) - bigger might also be fine.

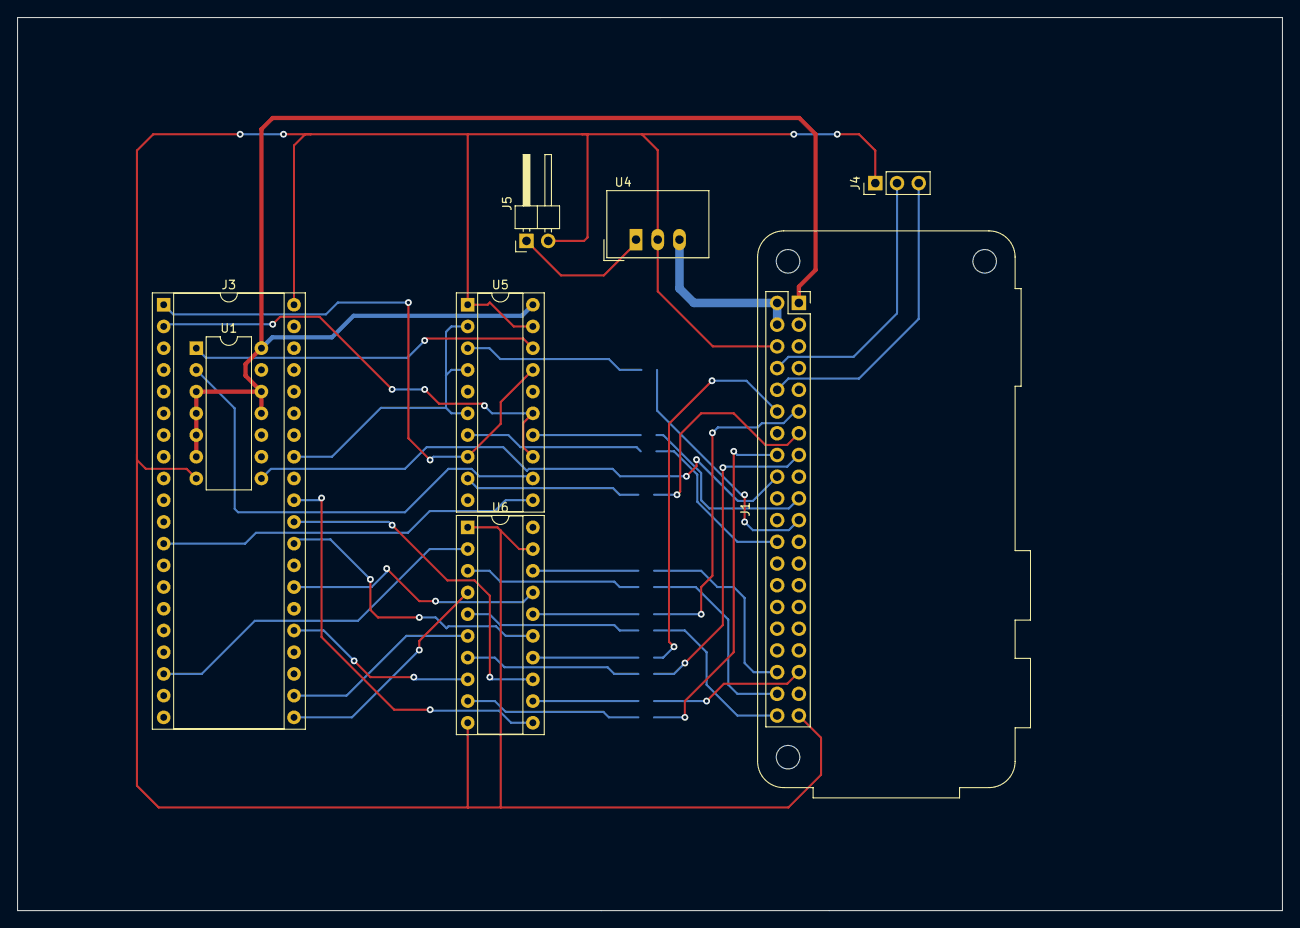
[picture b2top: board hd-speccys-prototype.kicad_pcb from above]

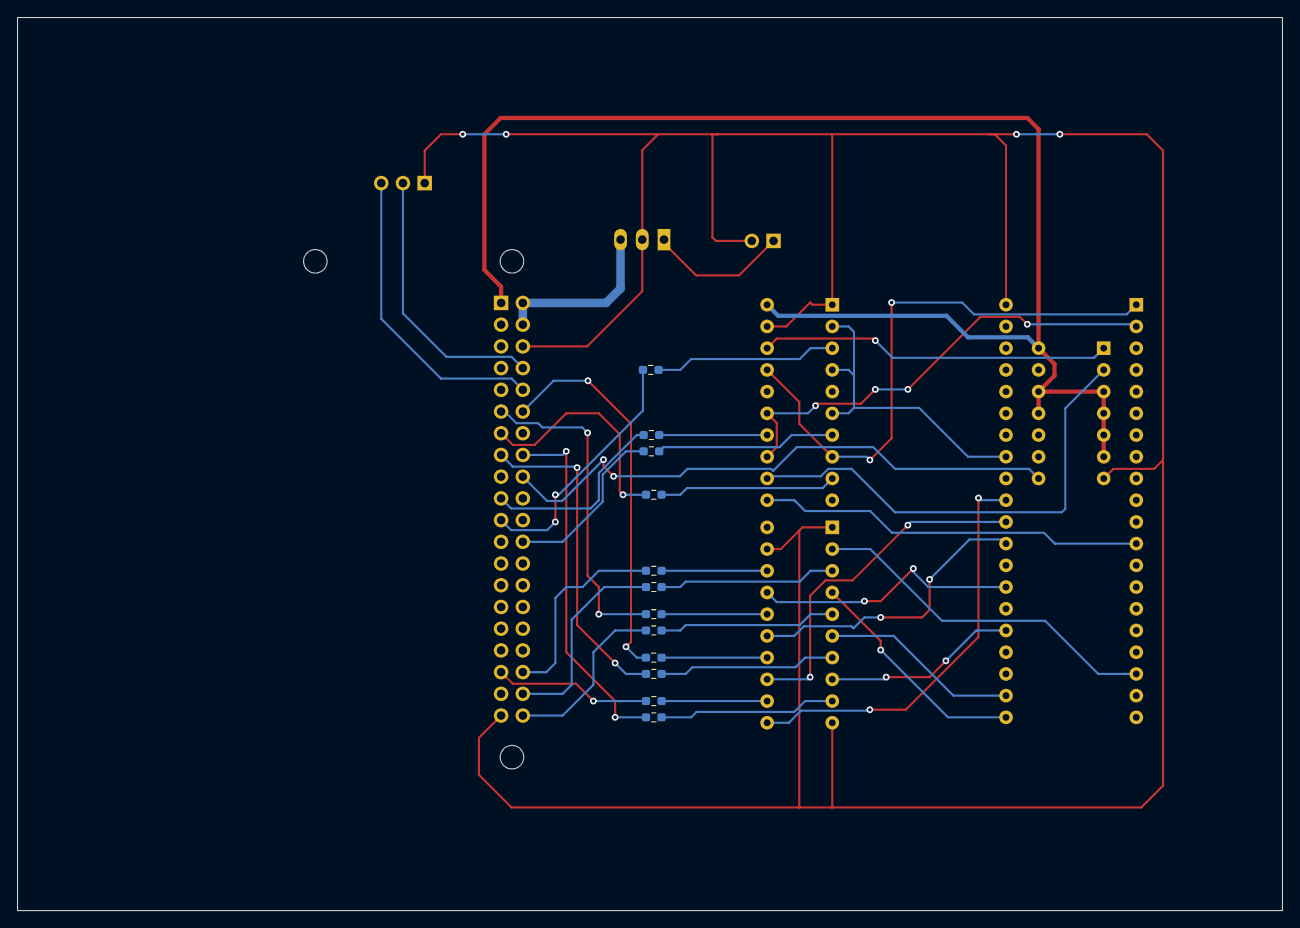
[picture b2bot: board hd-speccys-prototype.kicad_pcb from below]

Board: 2 copper layers, 148.0 x 104.5 mm, 20 parts (12 on the bottom side), 45 nets.

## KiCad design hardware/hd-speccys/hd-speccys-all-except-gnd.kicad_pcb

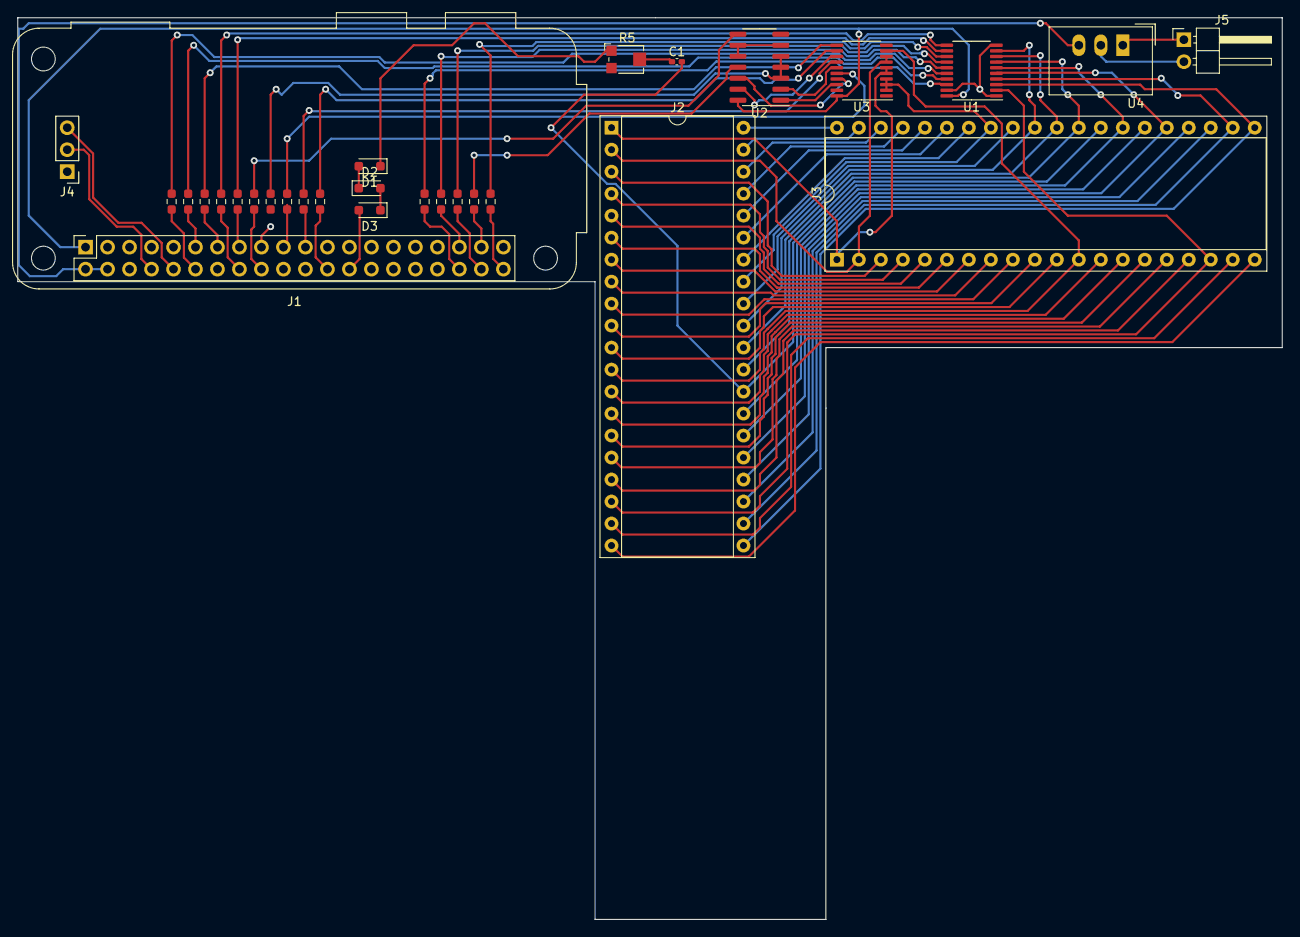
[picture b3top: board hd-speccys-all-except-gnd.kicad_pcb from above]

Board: 2 copper layers, 146.1 x 104.1 mm, 29 parts (0 on the bottom side), 84 nets.

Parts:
C1: 100nF; C_0402_1005Metric_Pad0.74x0.62mm_HandSolder
D1, D2, D3: 1N4148; D_SOD-323_HandSoldering
J1: PI_ZERO_2x20; Raspberry_Pi_Zero_Socketed_THT_FaceDown_MountingHoles
J2: ULA_ZX_02x20; DIP-40_W15.24mm_Socket
J3: ULA_SOCKET_02x20; DIP-40_W15.24mm_Socket
J4: Conn_01x03_Pin; PinHeader_1x03_P2.54mm_Vertical
J5: POWER 9-20VDC; PinHeader_1x02_P2.54mm_Horizontal
R1, R2, R3, R4, R6, R7, R8, R9, R10, R11, R12, R13, R14, R15, R16: R; R_0603_1608Metric_Pad0.98x0.95mm_HandSolder
R5: 1k; Potentiometer_Bourns_TC33X_Vertical
U1, U3: 74LS541; TSSOP-20_4.4x6.5mm_P0.65mm
U2: 74LS132; SOIC-14_3.9x8.7mm_P1.27mm
U4: TSR_1-2450; Converter_DCDC_TRACO_TSR-1_THT

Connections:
GND: J1.6 (GND), J1.9 (GND), J1.14 (GND), J1.20 (GND), J1.25 (GND), J1.30 (GND), J1.34 (GND), J1.39 (GND), J2.40 (GND), J3.40 (GND), J4.1 (GND), J5.2 (GND), U1.1 (G1), U1.10 (GND), U1.19 (G2), U2.7 (GND), U3.1 (G1), U3.10 (GND), U3.19 (G2), U4.2 (GND)
unnamed: C1.1, R5.2
unnamed: D1.2 (A), D2.1 (K)
unnamed: D1.1 (K), R5.1
unnamed: D2.2 (A), D3.1 (K)
unnamed: D3.2 (A), J1.26 (SWE_SRW_(GPIO7))
unnamed: J1.37 (GPIO26), R3.1
unnamed: J1.13 (GPIO27), R8.1
unnamed: J1.24 (SD0), R7.1
unnamed: J1.21 (SD1), R6.1
unnamed: J1.19 (SD2), R4.1
unnamed: J1.8 (SD6_(TXD0)), J4.2 (TXD)
unnamed: J1.10 (SD7_(RXD0)), J4.3 (RXD)
unnamed: J1.36 (SD8), R9.1
unnamed: J1.11 (SD9), R10.1
unnamed: J1.12 (SD10), R11.1
unnamed: J1.35 (SD11), R12.1
unnamed: J1.38 (SD12), R13.1
unnamed: J1.40 (SD13), R14.1
unnamed: J1.15 (SD14), R15.1
unnamed: J1.16 (SD15), R16.1
unnamed: J1.18 (SD16_(DREQ)), R1.1, R2.1
unnamed: J2.5 (A0), J3.5 (A0)
unnamed: J2.6 (A1), J3.6 (A1)
unnamed: J2.7 (A2), J3.7 (A2)
unnamed: J2.8 (A3), J3.8 (A3)
unnamed: J2.9 (A4), J3.9 (A4)
unnamed: J2.10 (A5), J3.10 (A5)
unnamed: J2.11 (A6), J3.11 (A6)
unnamed: J2.36 (A14), J3.36 (A14)
unnamed: J2.37 (A15), J3.37 (A15)
unnamed: J2.18 (D0), J3.18 (D0), U1.2 (A0)
unnamed: J2.21 (D1), J3.21 (D1), U1.3 (A1)
unnamed: J2.22 (D2), J3.22 (D2), U1.4 (A2)
unnamed: J2.25 (D3), J3.25 (D3), U1.5 (A3)
unnamed: J2.27 (D4), J3.27 (D4), U1.6 (A4)
unnamed: J2.29 (D5), J3.29 (D5), U1.7 (A5)
unnamed: J2.30 (D6), J3.30 (D6), U1.8 (A6)
unnamed: J2.31 (D7), J3.31 (D7), U1.9 (A7)
unnamed: J2.19 (KB0), J3.19 (KB0)
unnamed: J2.20 (KB1), J3.20 (KB1)
unnamed: J2.23 (KB2), J3.23 (KB2)
unnamed: J2.24 (KB3), J3.24 (KB3)
unnamed: J2.26 (KB4), J3.26 (KB4)
unnamed: C1.2, J2.28 (MIC_TAPE), J3.28 (MIC_TAPE)
unnamed: J2.39 (OSC), J3.39 (OSC)
unnamed: J2.15 (U), J3.15 (U)
unnamed: J2.16 (V), J3.16 (V)
unnamed: J2.14 (VCC_1), J3.14 (VCC_1)
unnamed: J2.13 (VCC_2), J3.13 (VCC_2)
unnamed: J2.17 (Y), J3.17 (Y)
unnamed: J2.1 (/CAS), J3.1 (/CAS), U3.5 (A3), U3.6 (A4)
unnamed: J2.32 (/CPU), J3.32 (/CPU)
unnamed: J2.4 (/DRAMWE), J3.4 (/DRAMWE)
unnamed: J2.12 (/INT), J3.12 (/INT), U3.9 (A7)
unnamed: J2.33 (/IOREQ), J3.33 (/IOREQ), U3.2 (A0), U3.3 (A1), U3.4 (A2)
unnamed: J2.38 (/MREQ), J3.38 (/MREQ)
unnamed: J2.35 (/RAS), J3.35 (/RAS)
unnamed: J2.3 (/RD), J3.3 (/RD)
unnamed: J2.34 (/ROMCS), J3.34 (/ROMCS)
unnamed: J2.2 (/WR), J3.2 (/WR), U3.7 (A5), U3.8 (A6)
unnamed: J5.1 (VCC), U4.1 (Vin)
unnamed: R1.2, U2.8
unnamed: R2.2, U2.3, U2.4, U2.5
unnamed: R3.2, U2.11
unnamed: R9.2, U1.18 (Y0)
unnamed: R10.2, U1.17 (Y1)
unnamed: R11.2, U1.16 (Y2)
unnamed: R12.2, U1.15 (Y3)
unnamed: R13.2, U1.14 (Y4)
unnamed: R14.2, U1.13 (Y5)
unnamed: R15.2, U1.12 (Y6)
unnamed: R16.2, U1.11 (Y7)
unnamed: U2.6, U2.9, U2.10
unnamed: U2.1, U3.18 (Y0)
unnamed: U2.12, U3.17 (Y1)
unnamed: R4.2, U3.16 (Y2)
unnamed: U2.2, U3.15 (Y3)
unnamed: R6.2, U3.14 (Y4)
unnamed: U2.13, U3.13 (Y5)
unnamed: R7.2, U3.12 (Y6)
unnamed: R8.2, U3.11 (Y7)
VDD: J1.2 (5V0), J1.4 (5V0), U4.3 (Vout)
VDDA: J1.1 (3V3), J1.17 (3V3), U1.20 (VCC), U2.14 (VCC), U3.20 (VCC)

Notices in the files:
hardware/hd-speccys-1_0a/hd-speccys-1_0a.kicad_pcb:
© 2023 RA SEWELL
